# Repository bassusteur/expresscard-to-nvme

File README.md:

# Expresscard to NVMe  
This ExpressCard to NVME adapter is an attempt to revive the Thinkmods project by making the design open source and following the original as closely as possible.

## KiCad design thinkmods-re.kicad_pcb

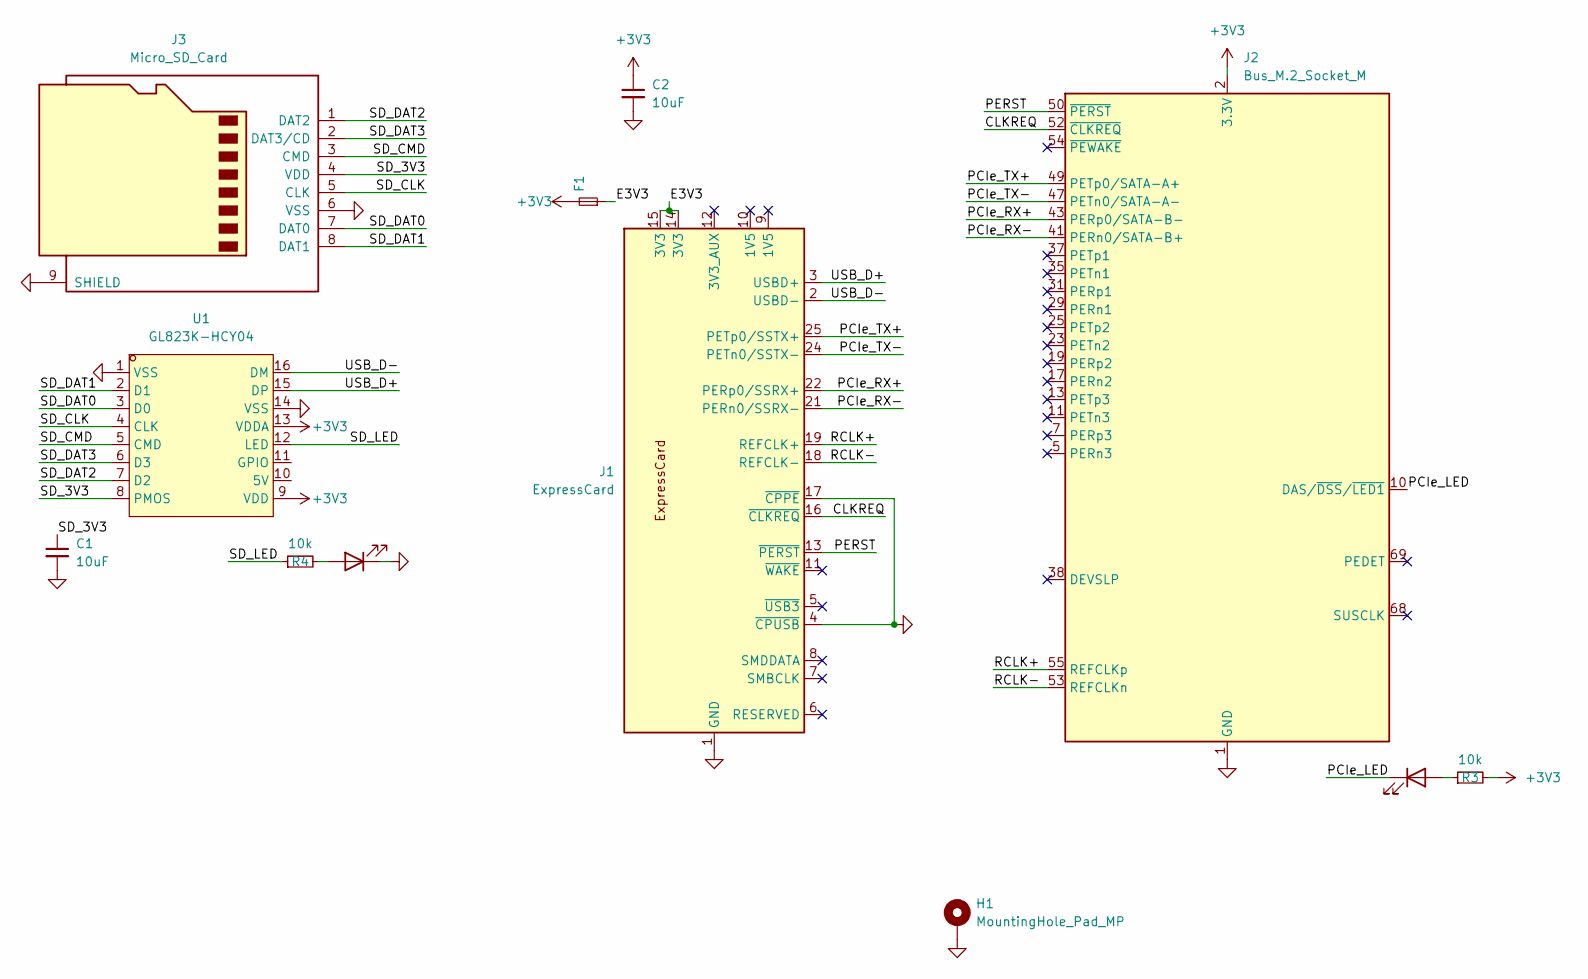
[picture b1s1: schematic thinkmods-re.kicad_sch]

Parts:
C1, C2: 10uF; C_0603_1608Metric
D1, D2: LED; LED_0603_1608Metric
F1: Fuse_Small; Fuse_0805_2012Metric
H1: MountingHole_Pad_MP; MountingHole_3.2mm_M3_Pad_small
J1: ExpressCard; ExpressCard_Plug
J2: Bus_M.2_Socket_M; CONN-SMD_APCI0159-P001A
J3: Micro_SD_Card; TF-SMD_TF-123-ARP9H15
R3, R4: 10k; R_0402_1005Metric
U1: GL823K-HCY04; SSOP-16_3.9x4.9mm_P0.635mm; LCSC Part C284879

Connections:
+3V3: C2.1, F1.2, J2.2 (3.3V), J2.4 (3.3V), J2.12 (3.3V), J2.14 (3.3V), J2.16 (3.3V), J2.18 (3.3V), J2.70 (3.3V), J2.72 (3.3V), J2.74 (3.3V), R3.2, U1.9 (VDD), U1.13 (VDDA)
/CLKREQ: J1.16 (~CLKREQ), J2.52 (~CLKREQ)
/E3V3: F1.1, J1.14 (3V3), J1.15 (3V3)
/PCIe_LED: D2.1 (K), J2.10 (DAS/~DSS/~LED1)
/PCIe_RX+: J1.22 (PERp0/SSRX+), J2.43 (PERp0/SATA-B-)
/PCIe_RX-: J1.21 (PERn0/SSRX-), J2.41 (PERn0/SATA-B+)
/PCIe_TX+: J1.25 (PETp0/SSTX+), J2.49 (PETp0/SATA-A+)
/PCIe_TX-: J1.24 (PETn0/SSTX-), J2.47 (PETn0/SATA-A-)
/PERST: J1.13 (~PERST), J2.50 (~PERST)
/RCLK+: J1.19 (REFCLK+), J2.55 (REFCLKp)
/RCLK-: J1.18 (REFCLK-), J2.53 (REFCLKn)
/SD_3V3: C1.1, J3.4 (VDD), U1.8 (PMOS)
/SD_CLK: J3.5 (CLK), U1.4 (CLK)
/SD_CMD: J3.3 (CMD), U1.5 (CMD)
/SD_DAT0: J3.7 (DAT0), U1.3 (D0)
/SD_DAT1: J3.8 (DAT1), U1.2 (D1)
/SD_DAT2: J3.1 (DAT2), U1.7 (D2)
/SD_DAT3: J3.2 (DAT3/CD), U1.6 (D3)
/SD_LED: R4.1, U1.12 (LED)
/USB_D+: J1.3 (USBD+), U1.15 (DP)
/USB_D-: J1.2 (USBD-), U1.16 (DM)
GND: C1.2, C2.2, D1.1 (K), H1.MP, J1.1 (GND), J1.4 (~CPUSB), J1.17 (~CPPE), J1.20 (GND), J1.23 (GND), J1.26 (GND), J2.1 (GND), J2.3 (GND), J2.9 (GND), J2.15 (GND), J2.21 (GND), J2.27 (GND), J2.33 (GND), J2.39 (GND), J2.45 (GND), J2.51 (GND), J2.57 (GND), J2.71 (GND), J2.73 (GND), J2.75 (GND), J3.6 (VSS), J3.9 (SHIELD), U1.1 (VSS), U1.14 (VSS)
unnamed: D1.2 (A), R4.2
unnamed: D2.2 (A), R3.1

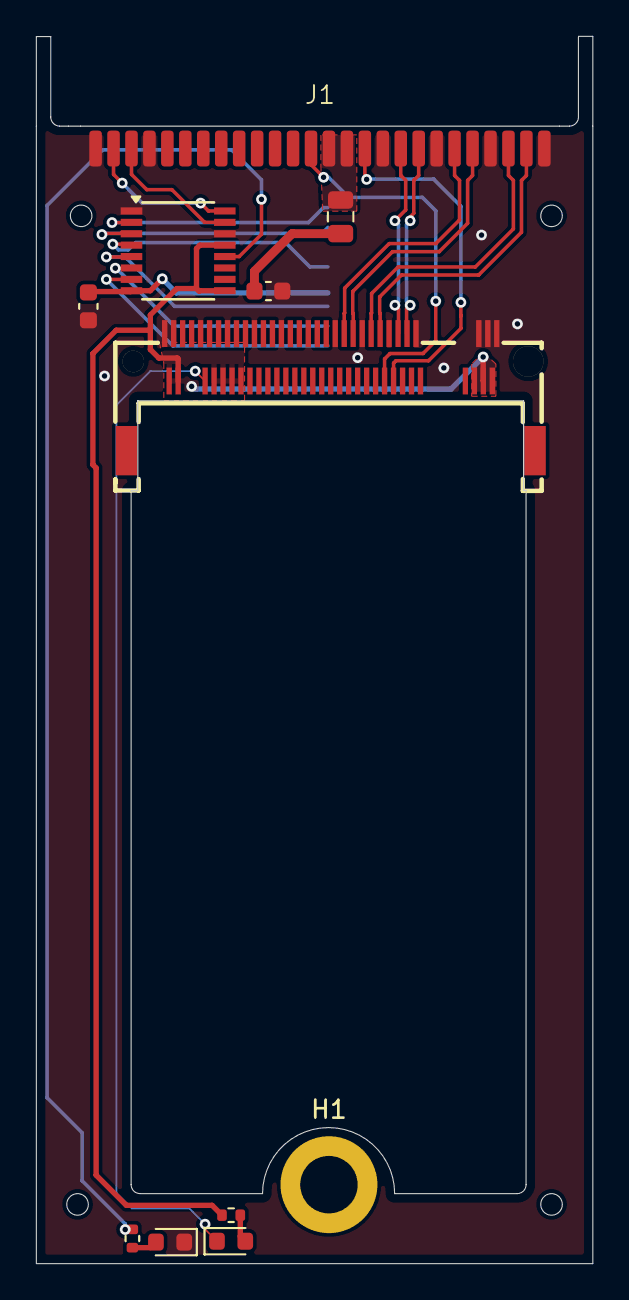
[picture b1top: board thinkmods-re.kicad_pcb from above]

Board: 2 copper layers, 31.0 x 68.4 mm, 12 parts (1 on the bottom side), 24 nets.
